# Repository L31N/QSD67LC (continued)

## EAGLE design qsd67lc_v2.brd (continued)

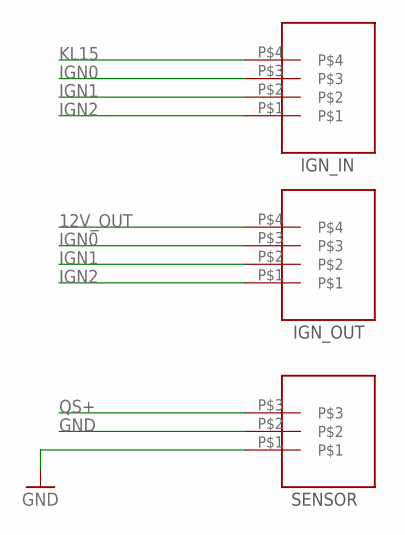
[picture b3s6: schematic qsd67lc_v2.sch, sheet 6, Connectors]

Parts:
CON1, CON2: RIA-AKL-230-04; CON-RIA-P4
CON3: RIA-AKL-230-03; CON-RIA-P3

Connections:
12V_OUT: CON2.P$4; also elsewhere on the board
GND: CON3.P$1, CON3.P$2; also elsewhere on the board
IGN0: CON1.P$3, CON2.P$3; also elsewhere on the board
IGN1: CON1.P$2, CON2.P$2
IGN2: CON1.P$1, CON2.P$1
KL15: CON1.P$4; also elsewhere on the board
QS+: CON3.P$3; also elsewhere on the board

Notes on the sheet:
IGN_IN
IGN_OUT
SENSOR

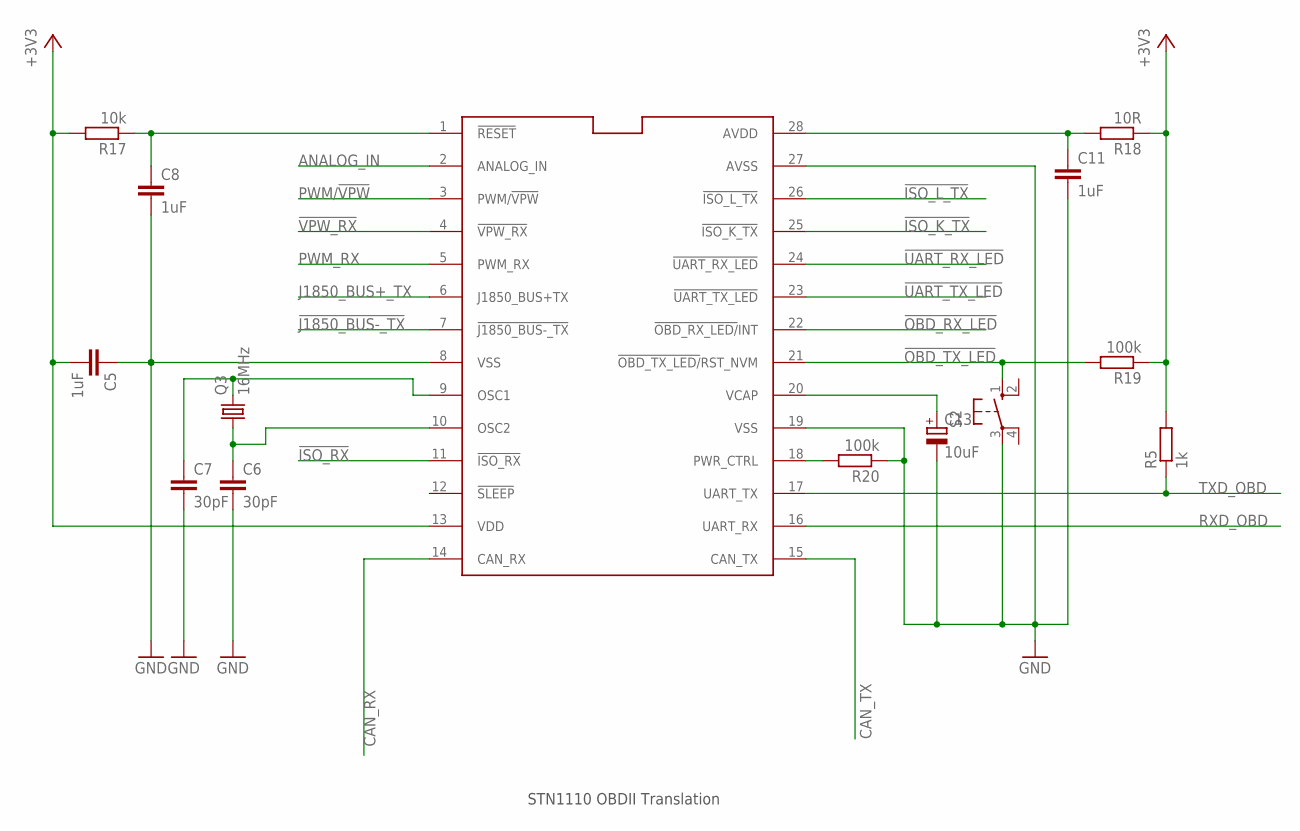
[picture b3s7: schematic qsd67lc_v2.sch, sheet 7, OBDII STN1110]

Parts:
C5, C8, C11: 1uF; C0805
C6, C7: 30pF; C0805
C13: 10uF; E2-5
Q3: 16MHz; HC49U-V
R5: 1k; R0805
R17: 10k; R0805
R18: 10R; R0805
R19, R20: 100k; R0805
S2: RST_NVM; B3F-10XX
U$1: STN1110-SOIC28; SOIC28L

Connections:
!ISO_K_TX: U$1.25 (!ISO_K_TX); also elsewhere on the board
!ISO_L_TX: U$1.26 (!ISO_L_TX); also elsewhere on the board
!ISO_RX: U$1.11 (!ISO_RX); also elsewhere on the board
!J1850_BUS-_TX: U$1.7 (!J1850_BUS-_TX); also elsewhere on the board
!OBD_RX_LED: U$1.22 (!OBD_RX_LED/!INT); also elsewhere on the board
!OBD_TX_LED: R19.2, S2.1 (S), U$1.21 (!OBD_TX_LED/!RST_NVM); also elsewhere on the board
!UART_RX_LED: U$1.24 (!UART_RX_LED); also elsewhere on the board
!UART_TX_LED: U$1.23 (!UART_TX_LED); also elsewhere on the board
!VPW_RX: U$1.4 (!VPW_RX); also elsewhere on the board
+3V3: C5.2, R5.2, R17.2, R18.1, R19.1, U$1.13 (VDD); also elsewhere on the board
ANALOG_IN: U$1.2 (ANALOG_IN)
CAN_RX: U$1.14 (CAN_RX); also elsewhere on the board
CAN_TX: U$1.15 (CAN_TX); also elsewhere on the board
GND: C5.1, C6.2, C7.2, C8.2, C11.2, C13.-, R20.1, S2.3, U$1.8 (VSS), U$1.19 (VSS), U$1.27 (AVSS); also elsewhere on the board
J1850_BUS+_TX: U$1.6 (J1850_BUS+TX); also elsewhere on the board
unnamed: C8.1, R17.1, U$1.1 (!RESET)
unnamed: C7.1, Q3.2, U$1.9 (OSC1)
unnamed: C11.1, R18.2, U$1.28 (AVDD)
unnamed: C6.1, Q3.1, U$1.10 (OSC2)
unnamed: C13.+, U$1.20 (VCAP)
unnamed: R20.2, U$1.18 (PWR_CTRL)
PWM/!VPW: U$1.3 (PWM/!VPW); also elsewhere on the board
PWM_RX: U$1.5 (PWM_RX); also elsewhere on the board
RXD_OBD: U$1.16 (UART_RX); also elsewhere on the board
TXD_OBD: R5.1, U$1.17 (UART_TX); also elsewhere on the board

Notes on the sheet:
STN1110 OBDII Translation

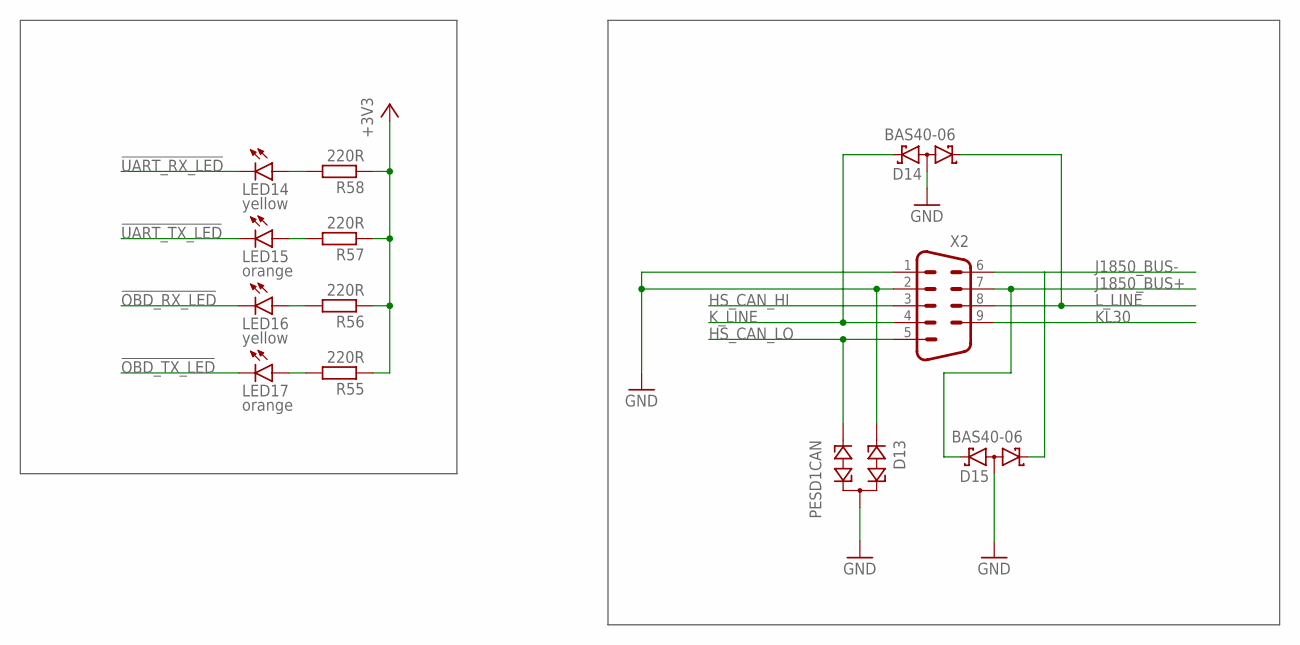
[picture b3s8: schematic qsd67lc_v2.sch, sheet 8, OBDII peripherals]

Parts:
D13: PESD1CAN; SOT23
D14, D15: BAS40-06; SOT23
LED14, LED16: yellow; CHIP-LED0805
LED15, LED17: orange; CHIP-LED0805
R55, R56, R57, R58: 220R; R0805
X2: M09HP

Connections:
!OBD_RX_LED: LED16.C; also elsewhere on the board
!OBD_TX_LED: LED17.C; also elsewhere on the board
!UART_RX_LED: LED14.C; also elsewhere on the board
!UART_TX_LED: LED15.C; also elsewhere on the board
+3V3: R55.1, R56.1, R57.1, R58.1; also elsewhere on the board
GND: D13.1, D13.3, D14.3 (AA), D15.3 (AA), X2.1, X2.2; also elsewhere on the board
HS_CAN_HI: X2.3; also elsewhere on the board
HS_CAN_LO: D13.2, X2.5; also elsewhere on the board
J1850_BUS+: D15.2 (K2), X2.7; also elsewhere on the board
J1850_BUS-: D15.1 (K1), X2.6; also elsewhere on the board
KL30: X2.9; also elsewhere on the board
K_LINE: D14.2 (K2), X2.4; also elsewhere on the board
L_LINE: D14.1 (K1), X2.8; also elsewhere on the board
unnamed: LED17.A, R55.2
unnamed: LED16.A, R56.2
unnamed: LED15.A, R57.2
unnamed: LED14.A, R58.2

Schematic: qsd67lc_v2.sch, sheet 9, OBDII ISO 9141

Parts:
IC9: LM339D; SO14
R59, R60, R61, R62: 10k; R0805
R63, R65: 510R 0W5; 0207/12
R64, R66: 1k; R0805
T8, T9: MMBT3904; SOT23-BEC

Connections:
!ISO_K_TX: R64.1; also elsewhere on the board
!ISO_L_TX: R66.1; also elsewhere on the board
!ISO_RX: IC9.2 (OUT), R62.2; also elsewhere on the board
+3V3: R62.1; also elsewhere on the board
+12V: IC9.3 (V+), R59.1, R63.1, R65.1; also elsewhere on the board
GND: IC9.12 (GND), R60.2, T8.E, T9.E; also elsewhere on the board
K_LINE: R61.1, R63.2, T8.C; also elsewhere on the board
L_LINE: R65.2, T9.C; also elsewhere on the board
unnamed: IC9.5 (+IN), R59.2, R60.1
unnamed: IC9.4 (-IN), R61.2
unnamed: R64.2, T8.B
unnamed: R66.2, T9.B

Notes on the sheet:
ISO 9141 / ISO 14230

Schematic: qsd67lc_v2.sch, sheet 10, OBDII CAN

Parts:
C24, C25, C26: 1uF; C0805
R67, R68: 100R; R0805
R69: 100k; R0805
U3: MCP2562-E/SN; SOIC127P600X175-8N

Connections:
+3V3: R69.2, U3.5 (VIO); also elsewhere on the board
+5V: C26.1, U3.3 (VDD); also elsewhere on the board
CAN_RX: U3.4 (RXD); also elsewhere on the board
CAN_TX: U3.1 (TXD); also elsewhere on the board
GND: C24.2, C25.2, C26.2, U3.2 (VSS); also elsewhere on the board
HS_CAN_HI: R67.2, U3.7 (CANH); also elsewhere on the board
HS_CAN_LO: R68.2, U3.6 (CANL); also elsewhere on the board
unnamed: C25.1, R68.1
unnamed: C24.1, R67.1
unnamed: R69.1, U3.8 (STBY)

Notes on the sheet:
High-Speed CAN

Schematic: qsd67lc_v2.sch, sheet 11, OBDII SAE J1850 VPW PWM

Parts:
C27: 100nF; C0805
D16, D17, D18: BAT54; SOT23
IC9: LM339D; SO14
IC10: LM317MSTT3; SOT223
Q5, Q8: BSS123; SOT23
Q7: BSS84; SOT23
R70, R78: 240R; R0805
R71, R84: 1k; R0805
R72: 430R; R0805
R73, R74, R75, R76, R79, R81, R82, R83: 10k; R0805
R77: 1k5; R0805
R80: 2k7; R0805
T11: BC847; SOT23

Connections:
!J1850_BUS-_TX: R84.2; also elsewhere on the board
!VPW_RX: IC9.14 (OUT), R82.2; also elsewhere on the board
+3V3: R75.1, R82.1; also elsewhere on the board
+5V: D18.1 (A), R80.1; also elsewhere on the board
+12V: C27.1, IC10.3 (IN); also elsewhere on the board
GND: C27.2, D17.3 (C), Q5.2 (S), Q8.2 (S), R72.1, R78.1, R81.2, T11.2 (E); also elsewhere on the board
J1850_BUS+: D16.3 (C), R73.2, R76.2, R79.2; also elsewhere on the board
J1850_BUS+_TX: Q8.1 (G), R78.2; also elsewhere on the board
J1850_BUS-: R74.2, R83.1, T11.3 (C); also elsewhere on the board
unnamed: IC10.1 (ADJ), R70.1, R71.2
unnamed: Q5.3 (D), R71.1, R72.2
unnamed: IC9.7 (+IN), R73.1
unnamed: IC9.6 (-IN), R74.1
unnamed: D16.1 (A), Q7.3 (D)
unnamed: D17.1 (A), R76.1
unnamed: Q7.1 (G), Q8.3 (D), R77.1
unnamed: IC9.9 (+IN), R79.1
unnamed: IC9.8 (-IN), R80.2, R81.1
unnamed: D18.3 (C), R83.2
unnamed: R84.1, T11.1 (B)
PWM/!VPW: Q5.1 (G); also elsewhere on the board
PWM_RX: IC9.1 (OUT), R75.2; also elsewhere on the board
V_J1850: IC10.4 (OUT), Q7.2 (S), R70.2, R77.2

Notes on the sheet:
SAE J1850 VPW / PWM

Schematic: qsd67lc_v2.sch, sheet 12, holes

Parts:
H1, H2, H3, H4: MOUNT-HOLE3.0; 3,0

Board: 2 copper layers, 143 parts (3 on the bottom side), 103 nets, no tracks yet.

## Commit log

2018-09-25 Backlink to CADLAB.io has been added.
2018-09-25 removed temp files
2018-09-25 added .gitignore file for eagle projects
2018-09-25 added mountholes added atmega8 (incl. leds, switches)
2018-09-25 changed supply from 5V to 3V3
2018-09-25 added hc05 circuits
2018-10-04 removed OBDII interface added ignition power circuit
2018-10-04 added rs232 for direct PC communication
2018-10-13 added connectors fixed rs232 dsub9 pinning added current supply circuit
2018-10-13 added correct connector devices
2018-10-13 started with the layout
2018-10-14 added zener diode for overvoltage protection
2018-10-14 added an ftdi chip to use usb directly instead of rs232 dsub connector
2018-10-15 working commit
2018-10-15 added galvanic decoupling for usb completed ftdi circuit
2018-10-15 replaced the 6n137 by an iso7221 because of 3V3 compatibility
2018-10-15 first placement of all parts
2018-10-15 working commit: * moved drill hole * removed 1 button * replaced status leds * moved ground planes
2018-10-15 routed ftdi part
2018-10-17 finished layout added some test probe pins to 3v3 12V and GND added lables to leds, connectors and pinheads
2018-10-17 added elcrow compatible gerber files
2019-02-11 started development of v2 prototype containing OBDII diagnostics capabilities.
2019-02-11 added ISO 9141 transceiver circuit
2019-02-11 implemented CAN and SAE 1850 driver circuits
2019-02-12 added k-line-adapter schematic and board finished first shot of qsd67lc_v2 schematic
2020-06-19 working on kline adapter ...
2020-06-19 removed doubled pullup resistor for QS+ (R14)
2020-06-19 replaced the 8 bit by an 16 bit timer to achieve longer measurement intervals
2020-06-19 rpm detection is basically working now restructuring setup mode to receive commands
2020-06-19 implemented the command detection in setup mode
2020-06-19 setupmode working now
2020-06-19 implemented a shifttime lookup table to vary the shifttime relative to rpm
2020-06-19 added eeprom readout of the threshold value
2020-06-19 added led indication weather threshold is reached or not
2020-06-22 inverted shift sensor signal -> working way on bike
2020-06-22 modified gitignore file to ignore some software related files (gcc / g++)
